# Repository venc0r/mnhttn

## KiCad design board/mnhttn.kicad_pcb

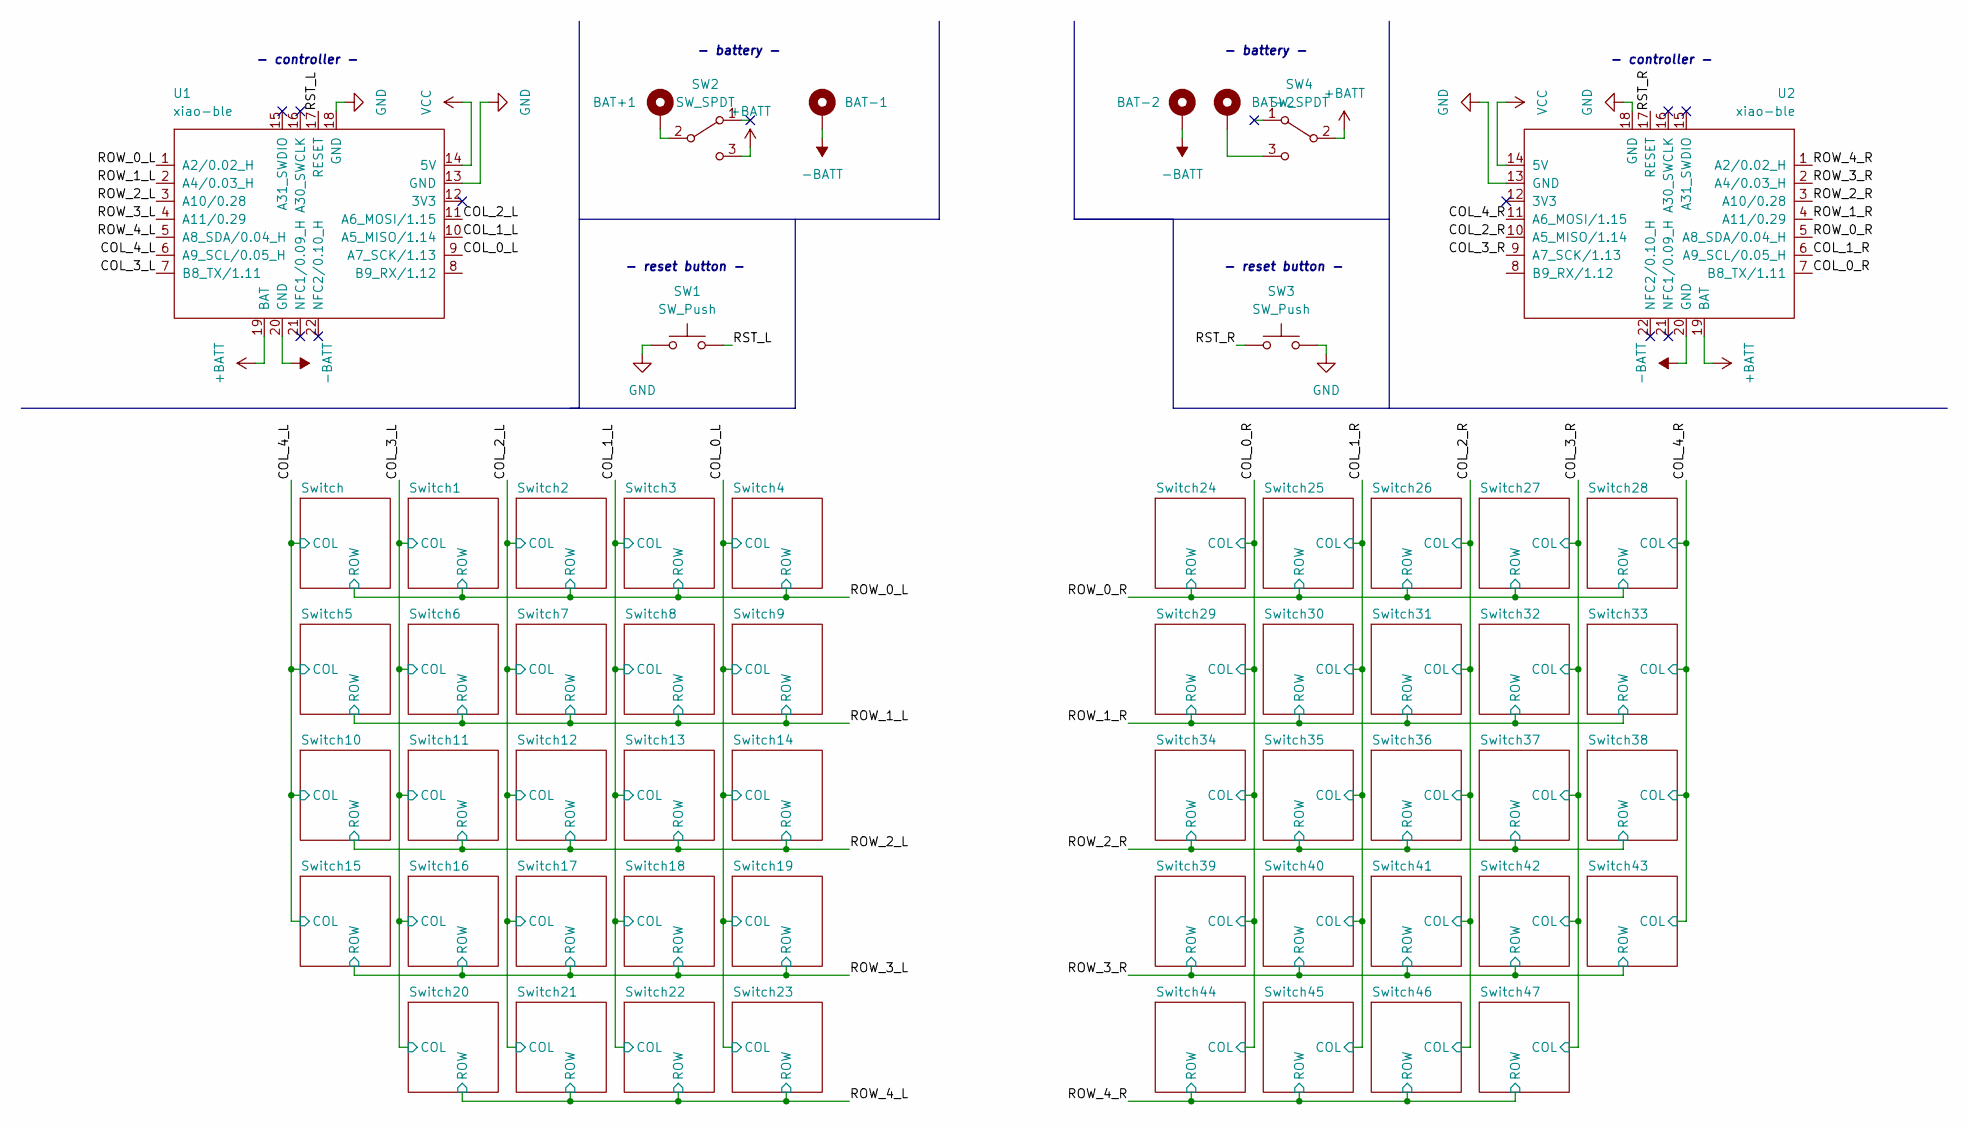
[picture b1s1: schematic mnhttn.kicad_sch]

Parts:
BAT+1, BAT+2: +; BatteryPad
BAT-1, BAT-2: -; BatteryPad
SW1, SW3: SW_Push; PushSwitch
SW2, SW4: SW_SPDT; MSK12C02
U1, U2: xiao-ble; xiao-ble-smd-cutout

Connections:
+BATT: SW2.3 (C), SW4.2 (B), U1.19 (BAT), U2.19 (BAT)
-BATT: BAT-1.1, BAT-2.1, U1.20 (GND), U2.20 (GND)
/COL_0_L: U1.9 (A7_SCK/1.13); also elsewhere on the board
/COL_0_R: U2.7 (B8_TX/1.11); also elsewhere on the board
/COL_1_L: U1.10 (A5_MISO/1.14); also elsewhere on the board
/COL_1_R: U2.6 (A9_SCL/0.05_H); also elsewhere on the board
/COL_2_L: U1.11 (A6_MOSI/1.15); also elsewhere on the board
/COL_2_R: U2.10 (A5_MISO/1.14); also elsewhere on the board
/COL_3_L: U1.7 (B8_TX/1.11); also elsewhere on the board
/COL_3_R: U2.9 (A7_SCK/1.13); also elsewhere on the board
/COL_4_L: U1.6 (A9_SCL/0.05_H); also elsewhere on the board
/COL_4_R: U2.11 (A6_MOSI/1.15); also elsewhere on the board
/ROW_0_L: U1.1 (A2/0.02_H); also elsewhere on the board
/ROW_0_R: U2.5 (A8_SDA/0.04_H); also elsewhere on the board
/ROW_1_L: U1.2 (A4/0.03_H); also elsewhere on the board
/ROW_1_R: U2.4 (A11/0.29); also elsewhere on the board
/ROW_2_L: U1.3 (A10/0.28); also elsewhere on the board
/ROW_2_R: U2.3 (A10/0.28); also elsewhere on the board
/ROW_3_L: U1.4 (A11/0.29); also elsewhere on the board
/ROW_3_R: U2.2 (A4/0.03_H); also elsewhere on the board
/ROW_4_L: U1.5 (A8_SDA/0.04_H); also elsewhere on the board
/ROW_4_R: U2.1 (A2/0.02_H); also elsewhere on the board
/RST_L: SW1.2, U1.17 (RESET)
/RST_R: SW3.2, U2.17 (RESET)
GND: SW1.1, SW3.1, U1.13 (GND), U1.18 (GND), U2.13 (GND), U2.18 (GND)
unnamed: BAT+1.1, SW2.2 (B)
unnamed: BAT+2.1, SW4.3 (C)
VCC: U1.14 (5V), U2.14 (5V)

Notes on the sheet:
- reset button -
- battery -
- controller -

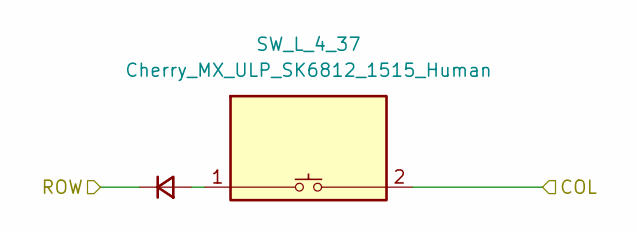
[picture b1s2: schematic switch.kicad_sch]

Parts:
D_L_4_37: D_Small; Diode_SOD123
SW_L_4_37: Cherry_MX_ULP_SK6812_1515_Human; Cherry_MX_ULP_Human

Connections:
/COL_2_R: SW_L_4_37.2; also elsewhere on the board
/ROW_2_R: D_L_4_37.1 (K); also elsewhere on the board
unnamed: D_L_4_37.2 (A), SW_L_4_37.1

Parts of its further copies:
D_L_4_1, D_L_4_2, D_L_4_3, D_L_4_4, D_L_4_5, D_L_4_6, D_L_4_7, D_L_4_8, D_L_4_9, D_L_4_10, D_L_4_11, D_L_4_12, D_L_4_13, D_L_4_14, D_L_4_15, D_L_4_16, D_L_4_17, D_L_4_18, D_L_4_19, D_L_4_20, D_L_4_21, D_L_4_22, D_L_4_23, D_L_4_24, D_L_4_25, D_L_4_26, D_L_4_27, D_L_4_28, D_L_4_29, D_L_4_30, D_L_4_31, D_L_4_32, D_L_4_33, D_L_4_34, D_L_4_35, D_L_4_36, D_L_4_38, D_L_4_39, D_L_4_40, D_L_4_41, D_L_4_42, D_L_4_43, D_L_4_44, D_L_4_45, D_L_4_46, D_L_4_47, D_L_4_48: D_Small; Diode_SOD123
SW_L_4_1, SW_L_4_2, SW_L_4_3, SW_L_4_4, SW_L_4_5, SW_L_4_6, SW_L_4_7, SW_L_4_8, SW_L_4_9, SW_L_4_10, SW_L_4_11, SW_L_4_12, SW_L_4_13, SW_L_4_14, SW_L_4_15, SW_L_4_16, SW_L_4_17, SW_L_4_18, SW_L_4_19, SW_L_4_20, SW_L_4_21, SW_L_4_22, SW_L_4_23, SW_L_4_24, SW_L_4_25, SW_L_4_26, SW_L_4_27, SW_L_4_28, SW_L_4_29, SW_L_4_30, SW_L_4_31, SW_L_4_32, SW_L_4_33, SW_L_4_34, SW_L_4_35, SW_L_4_36, SW_L_4_38, SW_L_4_39, SW_L_4_40, SW_L_4_41, SW_L_4_42, SW_L_4_43, SW_L_4_44, SW_L_4_45, SW_L_4_46, SW_L_4_47, SW_L_4_48: Cherry_MX_ULP_SK6812_1515_Human; Cherry_MX_ULP_Human

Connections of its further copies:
/COL_0_L: SW_L_4_4.2, SW_L_4_7.2, SW_L_4_10.2, SW_L_4_18.2, SW_L_4_26.2; also elsewhere on the board
/COL_0_R: SW_L_4_22.2, SW_L_4_34.2, SW_L_4_36.2, SW_L_4_40.2, SW_L_4_45.2; also elsewhere on the board
/COL_1_L: SW_L_4_3.2, SW_L_4_6.2, SW_L_4_14.2, SW_L_4_25.2, SW_L_4_31.2; also elsewhere on the board
/COL_1_R: SW_L_4_28.2, SW_L_4_29.2, SW_L_4_32.2, SW_L_4_41.2, SW_L_4_46.2; also elsewhere on the board
/COL_2_L: SW_L_4_8.2, SW_L_4_12.2, SW_L_4_17.2, SW_L_4_21.2, SW_L_4_30.2; also elsewhere on the board
/COL_2_R: SW_L_4_24.2, SW_L_4_33.2, SW_L_4_42.2, SW_L_4_47.2; also elsewhere on the board
/COL_3_L: SW_L_4_5.2, SW_L_4_13.2, SW_L_4_16.2, SW_L_4_19.2, SW_L_4_20.2; also elsewhere on the board
/COL_3_R: SW_L_4_23.2, SW_L_4_35.2, SW_L_4_38.2, SW_L_4_43.2, SW_L_4_48.2; also elsewhere on the board
/COL_4_L: SW_L_4_2.2, SW_L_4_9.2, SW_L_4_11.2, SW_L_4_15.2; also elsewhere on the board
/COL_4_R: SW_L_4_1.2, SW_L_4_27.2, SW_L_4_39.2, SW_L_4_44.2; also elsewhere on the board
/ROW_0_L: D_L_4_2.1 (K), D_L_4_3.1 (K), D_L_4_4.1 (K), D_L_4_19.1 (K), D_L_4_21.1 (K); also elsewhere on the board
/ROW_0_R: D_L_4_1.1 (K), D_L_4_24.1 (K), D_L_4_29.1 (K), D_L_4_35.1 (K), D_L_4_36.1 (K); also elsewhere on the board
/ROW_1_L: D_L_4_5.1 (K), D_L_4_6.1 (K), D_L_4_7.1 (K), D_L_4_8.1 (K), D_L_4_9.1 (K); also elsewhere on the board
/ROW_1_R: D_L_4_23.1 (K), D_L_4_27.1 (K), D_L_4_32.1 (K), D_L_4_33.1 (K), D_L_4_34.1 (K); also elsewhere on the board
/ROW_2_L: D_L_4_10.1 (K), D_L_4_11.1 (K), D_L_4_12.1 (K), D_L_4_13.1 (K), D_L_4_14.1 (K); also elsewhere on the board
/ROW_2_R: D_L_4_22.1 (K), D_L_4_28.1 (K), D_L_4_38.1 (K), D_L_4_39.1 (K); also elsewhere on the board
/ROW_3_L: D_L_4_15.1 (K), D_L_4_16.1 (K), D_L_4_17.1 (K), D_L_4_18.1 (K), D_L_4_25.1 (K); also elsewhere on the board
/ROW_3_R: D_L_4_40.1 (K), D_L_4_41.1 (K), D_L_4_42.1 (K), D_L_4_43.1 (K), D_L_4_44.1 (K); also elsewhere on the board
/ROW_4_L: D_L_4_20.1 (K), D_L_4_26.1 (K), D_L_4_30.1 (K), D_L_4_31.1 (K); also elsewhere on the board
/ROW_4_R: D_L_4_45.1 (K), D_L_4_46.1 (K), D_L_4_47.1 (K), D_L_4_48.1 (K); also elsewhere on the board
unnamed: D_L_4_1.2 (A), SW_L_4_1.1
unnamed: D_L_4_2.2 (A), SW_L_4_2.1
unnamed: D_L_4_3.2 (A), SW_L_4_3.1
unnamed: D_L_4_4.2 (A), SW_L_4_4.1
unnamed: D_L_4_5.2 (A), SW_L_4_5.1
unnamed: D_L_4_6.2 (A), SW_L_4_6.1
unnamed: D_L_4_7.2 (A), SW_L_4_7.1
unnamed: D_L_4_8.2 (A), SW_L_4_8.1
unnamed: D_L_4_9.2 (A), SW_L_4_9.1
unnamed: D_L_4_10.2 (A), SW_L_4_10.1
unnamed: D_L_4_11.2 (A), SW_L_4_11.1
unnamed: D_L_4_12.2 (A), SW_L_4_12.1
unnamed: D_L_4_13.2 (A), SW_L_4_13.1
unnamed: D_L_4_14.2 (A), SW_L_4_14.1
unnamed: D_L_4_15.2 (A), SW_L_4_15.1
unnamed: D_L_4_16.2 (A), SW_L_4_16.1
unnamed: D_L_4_17.2 (A), SW_L_4_17.1
unnamed: D_L_4_18.2 (A), SW_L_4_18.1
unnamed: D_L_4_19.2 (A), SW_L_4_19.1
unnamed: D_L_4_20.2 (A), SW_L_4_20.1
unnamed: D_L_4_21.2 (A), SW_L_4_21.1
unnamed: D_L_4_22.2 (A), SW_L_4_22.1
unnamed: D_L_4_23.2 (A), SW_L_4_23.1
unnamed: D_L_4_24.2 (A), SW_L_4_24.1
unnamed: D_L_4_25.2 (A), SW_L_4_25.1
unnamed: D_L_4_26.2 (A), SW_L_4_26.1
unnamed: D_L_4_27.2 (A), SW_L_4_27.1
unnamed: D_L_4_28.2 (A), SW_L_4_28.1
unnamed: D_L_4_29.2 (A), SW_L_4_29.1
unnamed: D_L_4_30.2 (A), SW_L_4_30.1
unnamed: D_L_4_31.2 (A), SW_L_4_31.1
unnamed: D_L_4_32.2 (A), SW_L_4_32.1
unnamed: D_L_4_33.2 (A), SW_L_4_33.1
unnamed: D_L_4_34.2 (A), SW_L_4_34.1
unnamed: D_L_4_35.2 (A), SW_L_4_35.1
unnamed: D_L_4_36.2 (A), SW_L_4_36.1
unnamed: D_L_4_38.2 (A), SW_L_4_38.1
unnamed: D_L_4_39.2 (A), SW_L_4_39.1
unnamed: D_L_4_40.2 (A), SW_L_4_40.1
unnamed: D_L_4_41.2 (A), SW_L_4_41.1
unnamed: D_L_4_42.2 (A), SW_L_4_42.1
unnamed: D_L_4_43.2 (A), SW_L_4_43.1
unnamed: D_L_4_44.2 (A), SW_L_4_44.1
unnamed: D_L_4_45.2 (A), SW_L_4_45.1
unnamed: D_L_4_46.2 (A), SW_L_4_46.1
unnamed: D_L_4_47.2 (A), SW_L_4_47.1
unnamed: D_L_4_48.2 (A), SW_L_4_48.1

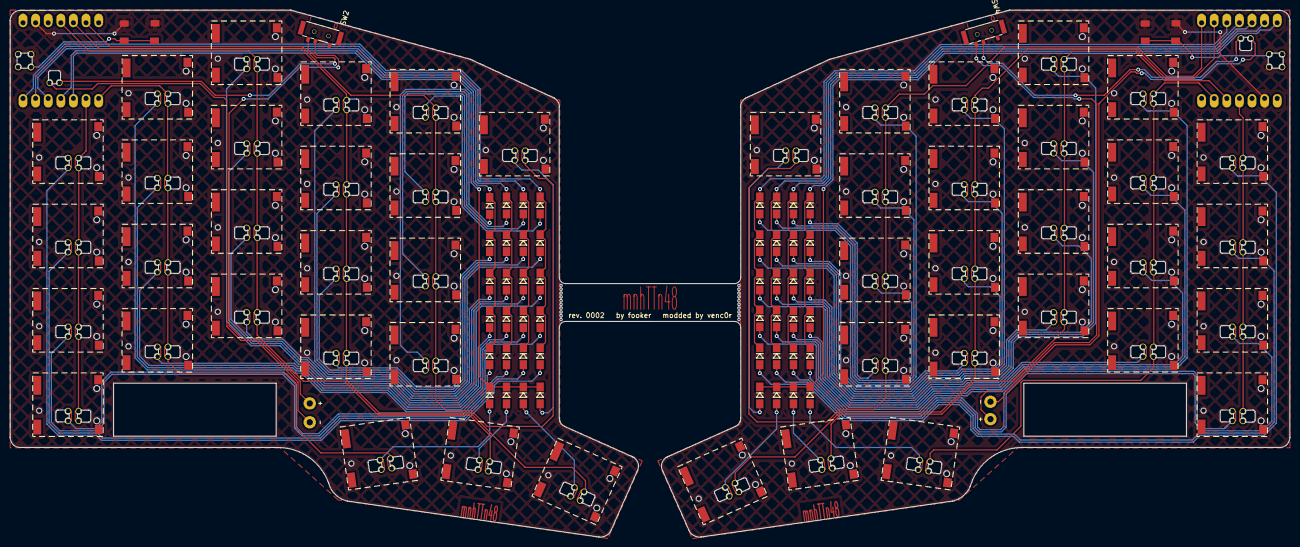
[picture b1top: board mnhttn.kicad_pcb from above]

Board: 2 copper layers, 257.9 x 106.2 mm, 108 parts (0 on the bottom side), 76 nets.

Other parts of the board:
MB1, MB2: MouseBites_10x0.5mm_P0.76mm
